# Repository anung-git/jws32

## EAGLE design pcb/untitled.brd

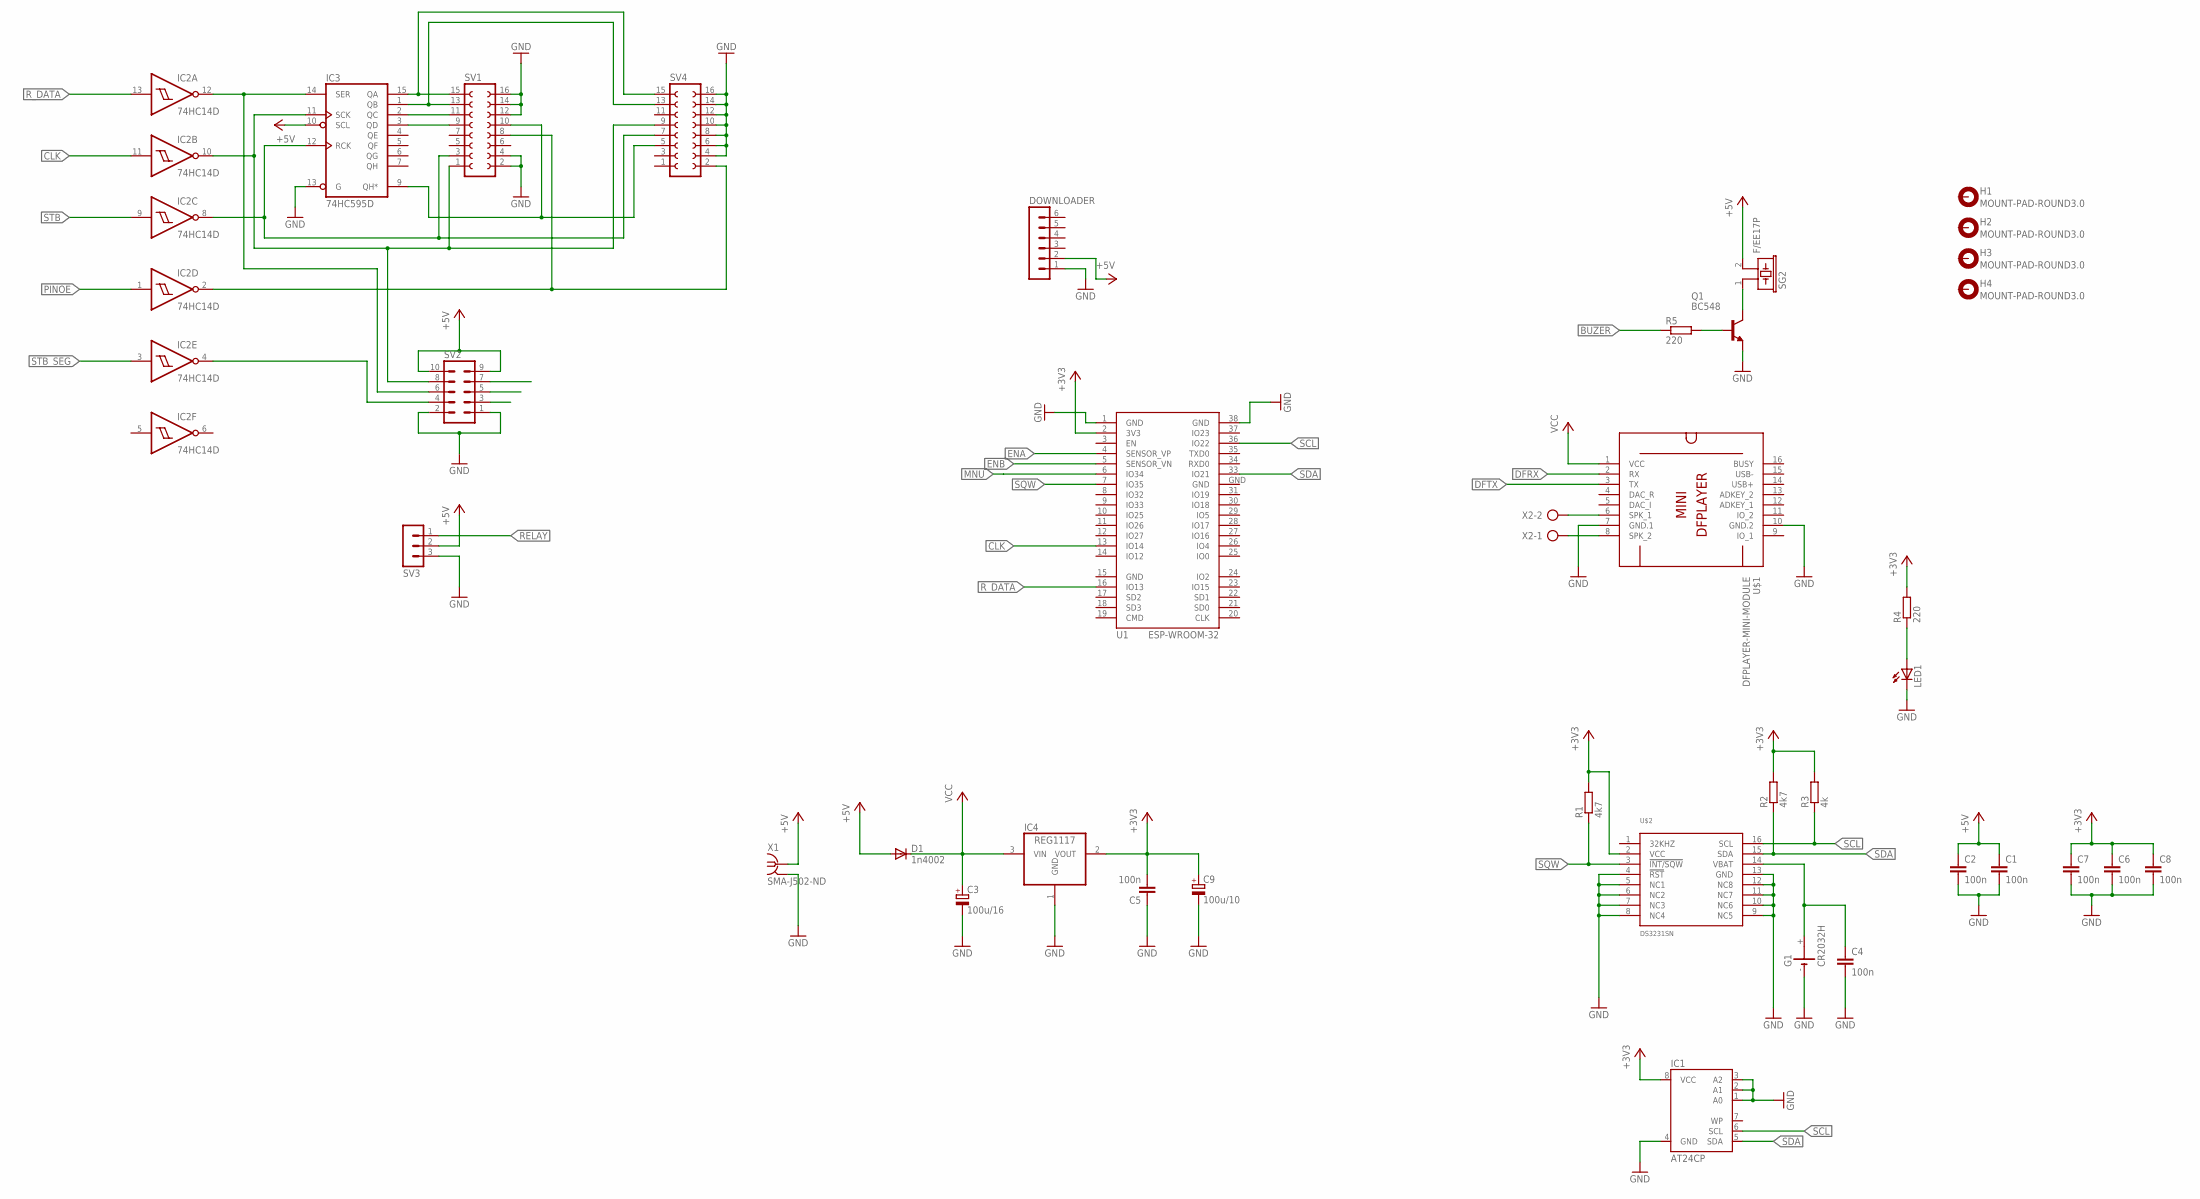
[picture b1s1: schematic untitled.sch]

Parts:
C1, C2, C4, C5, C6, C7, C8: 100n; C025-025X050
C3: 100u/16; E2,5-6
C9: 100u/10; E2,5-5
D1: 1n4002; DO35-10
DOWNLOADER: MA06-1
G1: CR2032H
H1, H2, H3, H4: MOUNT-PAD-ROUND3.0; 3,0-PAD
IC1: AT24CP; DIL08
IC2: 74HC14D; SO14
IC3: 74HC595D; SO16
IC4: REG1117; SOT223
LED1: LED3MM
Q1: BC548; TO92-EBC
R1, R2: 4k7; 0207/7
R3: 4k; 0207/7
R4, R5: 220; 0207/7
SG2: F/EE17P
SV1, SV4: FE08-2
SV2: MA05-2
SV3: MA03-1
U1: ESP-WROOM-32
U$1: DFPLAYER-MINI-MODULE
U$2: DS3231SN; SO16W
X1: SMA-J502-ND; J502-ND
X2: AK500/2-H

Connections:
+3V3: C5.2, C6.1, C7.1, C8.1, C9.+, IC1.8 (VCC), IC4.2 (VOUT), R1.2, R2.2, R3.2, R4.2, U1.2 (3V3), U$2.2 (VCC)
+5V: C1.1, C2.1, D1.A, DOWNLOADER.2, IC3.10 (SCL), SG2.2, SV2.9, SV2.10, SV3.2, X1.3 (1), X1.4 (1)
BUZER: R5.1
CLK: IC2.11 (I), U1.13 (IO14)
DFRX: U$1.2 (RX)
DFTX: U$1.3 (TX)
ENA: U1.4 (SENSOR_VP)
ENB: U1.5 (SENSOR_VN)
GND: C1.2, C2.2, C3.-, C4.2, C5.1, C6.2, C7.2, C8.2, C9.-, DOWNLOADER.1, G1.-, IC1.1 (A0), IC1.2 (A1), IC1.3 (A2), IC1.4 (GND), IC2.7 (GND), IC3.8 (GND), IC3.13 (G), IC4.1 (GND), LED1.K (C), Q1.E, SV1.2, SV1.4, SV1.12, SV1.14, SV1.16, SV2.1, SV2.2, SV3.3, SV4.4, SV4.6, SV4.8, SV4.10, SV4.12, SV4.14, SV4.16, U1.1 (GND), U1.15 (GND), U1.38 (GND), U1.GND, U$1.7 (GND.1), U$1.10 (GND.2), U$2.4 (!RST), U$2.5 (NC1), U$2.6 (NC2), U$2.7 (NC3), U$2.8 (NC4), U$2.9 (NC5), U$2.10 (NC6), U$2.11 (NC7), U$2.12 (NC8), U$2.13 (GND), X1.2, X1.5 (2)
MNU: U1.6 (IO34)
unnamed: Q1.C, SG2.1
unnamed: C4.1, G1.+, U$2.14 (VBAT)
unnamed: Q1.B, R5.2
unnamed: LED1.A, R4.1
unnamed: U$1.6 (SPK_1), X2.2
unnamed: U$1.8 (SPK_2), X2.1
unnamed: IC2.12 (O), IC3.14 (SER), SV2.6
unnamed: IC2.10 (O), IC3.11 (SCK), SV1.1, SV2.8, SV4.9
unnamed: IC2.8 (O), IC3.12 (RCK), SV1.3, SV4.7
unnamed: IC3.15 (QA), SV1.15, SV4.15
unnamed: IC3.1 (QB), SV1.13, SV4.13
unnamed: IC3.2 (QC), SV1.11
unnamed: IC3.3 (QD), SV1.9
unnamed: IC2.2 (O), SV1.8, SV4.2
unnamed: IC3.9 (QH*), SV1.10, SV4.5
unnamed: IC2.4 (O), SV2.4
PINOE: IC2.1 (I)
RELAY: SV3.1
R_DATA: IC2.13 (I), U1.16 (IO13)
SCL: IC1.6 (SCL), R3.1, U1.36 (IO22), U$2.16 (SCL)
SDA: IC1.5 (SDA), R2.1, U1.33 (IO21), U$2.15 (SDA)
SQW: R1.1, U1.7 (IO35), U$2.3 (!INT/SQW)
STB: IC2.9 (I)
STB_SEG: IC2.3 (I)
VCC: C3.+, D1.C, IC2.14 (VCC), IC3.16 (VCC), IC4.3 (VIN), U$1.1 (VCC)

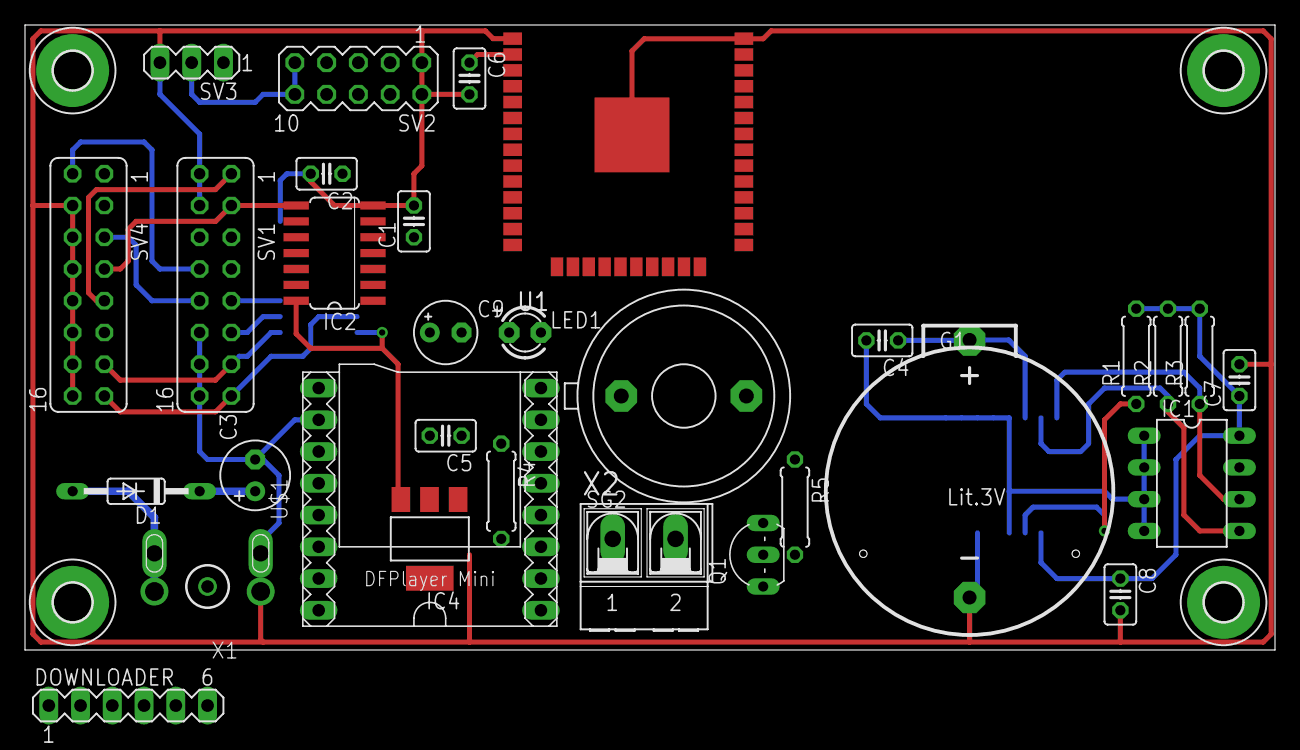
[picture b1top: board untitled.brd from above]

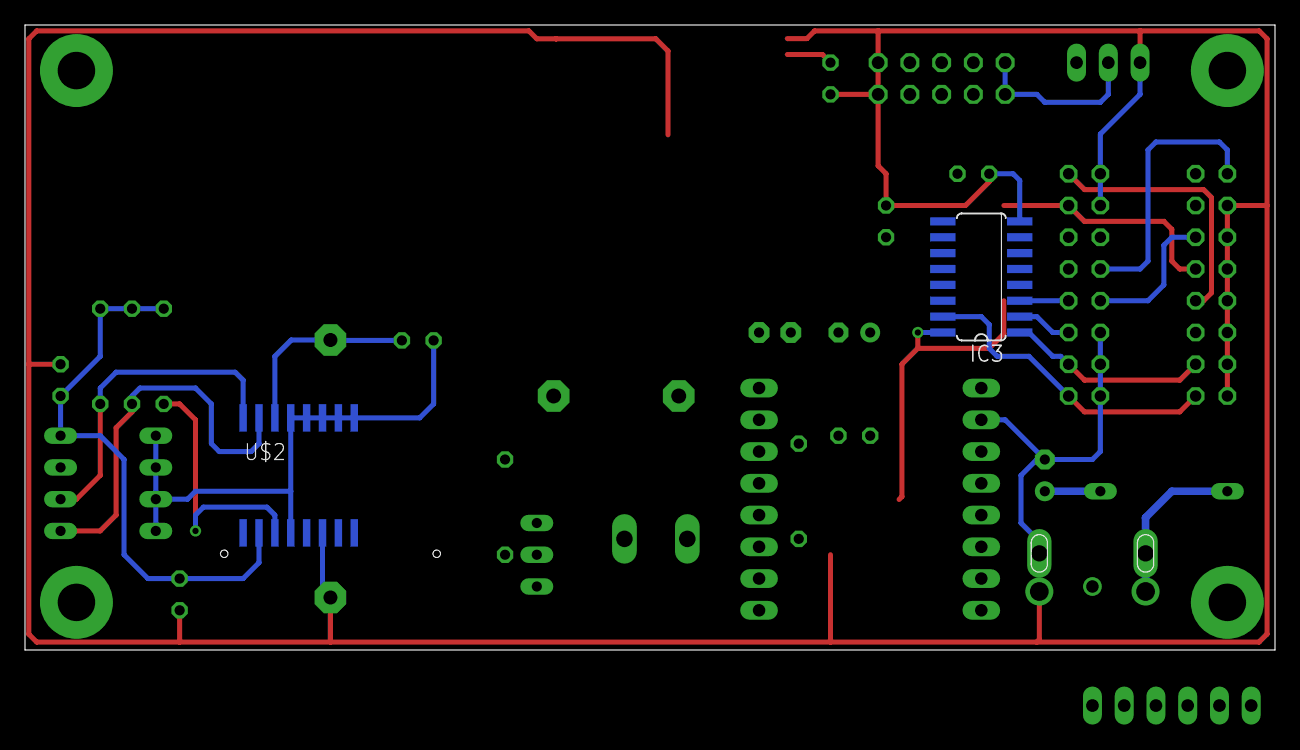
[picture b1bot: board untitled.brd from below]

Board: 2 copper layers, 100.0 x 50.0 mm, 37 parts (2 on the bottom side), 25 nets.

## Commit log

2021-02-28 upload
2021-02-28 test
2021-02-28 dfplayer
2021-02-28 include dmd
2021-03-01 kalender
2021-03-01 adzan + iqomah
2021-03-01 iqomah
2021-03-01 dmd config
2021-03-04 relayout
2021-03-05 android app
2021-03-05 layout pcb
2021-03-07 mvvm
2021-03-08 home view
2021-03-11 set fix
2021-03-12 set brightnes
2021-03-13 Brightnes Slider
2021-03-13 appbar color

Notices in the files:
parts and their libraries:
ESP32: Creative Commons Attribution-ShareAlike 4.0 International
